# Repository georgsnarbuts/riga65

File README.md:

# riga65

<br />This work is licensed under a <a rel="license" href="http://creativecommons.org/licenses/by-nc/4.0/">Creative Commons Attribution-NonCommercial 4.0 International License</a>.  

a 65 % keyboard

A custom 65% mechanical keyboard with 100% through hole component assembly.  
Running atMega 32a MCU.  
Featuring a 128x32 oled display and an optional rotary encoder. Running QMK.    
  
Sample board built with gateron yellow switches (filmed and lubed with krytox 205 grade 0) and durock stabilizers.

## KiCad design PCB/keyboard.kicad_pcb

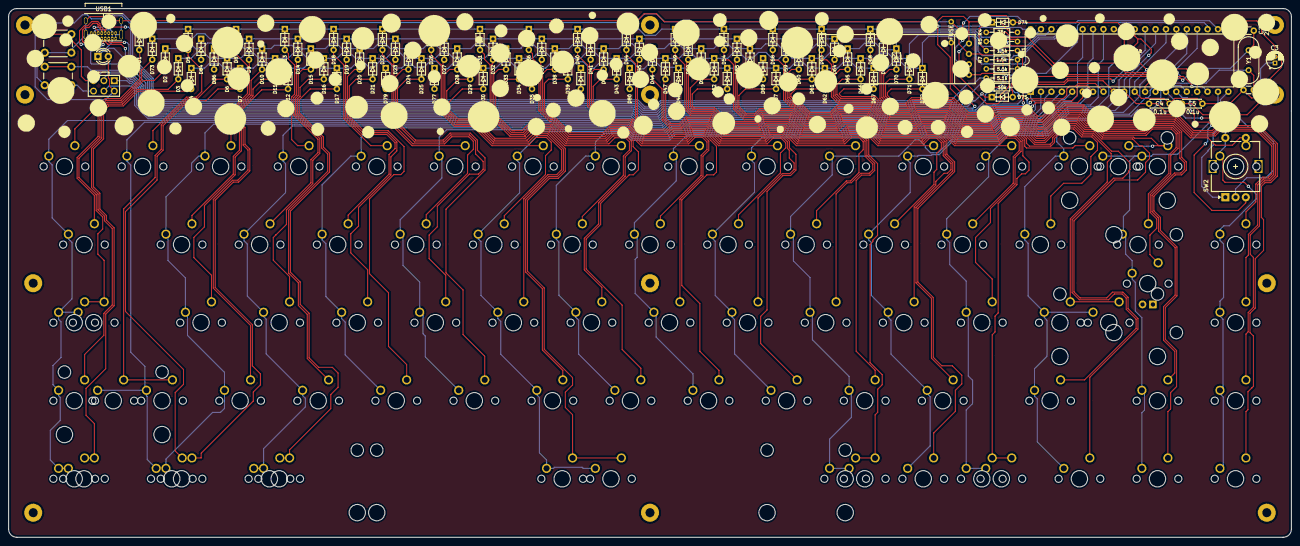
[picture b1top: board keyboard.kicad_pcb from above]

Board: 2 copper layers, 313.0 x 129.0 mm, 185 parts (0 on the bottom side), 114 nets.

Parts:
C1, C2: 22p; C_Disc_D3.0mm_W1.6mm_P2.50mm
C3: 4.7u; CP_Radial_D4.0mm_P1.50mm
C4, C5: 0.1u; C_Disc_D4.3mm_W1.9mm_P5.00mm
D1, D2, D3, D4, D5, D6, D7, D8, D9, D10, D11, D12, D13, D14, D15, D16, D17, D18, D19, D20, D21, D22, D23, D24, D25, D26, D27, D28, D29, D30, D31, D32, D33, D34, D35, D36, D37, D38, D39, D40, D41, D42, D43, D44, D45, D46, D47, D48, D49, D50, D51, D52, D53, D54, D55, D56, D57, D58, D59, D60, D61, D62, D63, D64, D65, D66, D67, D68, D69, D70, D71, D72, D73, D77, D79, D80, D81, D84, D86, D89: 1N4148; D_DO-35_SOD27_P5.08mm_Horizontal
D74, D75: D_Zener_Small; D_DO-35_SOD27_P5.08mm_Horizontal
D76: LED; LED_D3.0mm
F1: 500mA; polyfuse_5.1mm
J1: AVR-ISP-6; AVR_ICSP_3x2
K_1.5U_LALT1, K_1.5U_LCTRL1, K_1.5U_RALT1, K_1.5U_RCTRL1: KEYSW; MXOnly-1.5U-NoLED
K_1.25U_LALT1, K_1.25U_LCNTRL1, K_1.25U_LWIN1: KEYSW; MXOnly-1.25U-NoLED
K_1U_BACKSPACE1, K_1U_LCTRL1, K_1U_RALT1, K_1U_RCTRL1, K_1U_RWIN1, K_.1: KEYSW; MXOnly-1U-NoLED
K_2U_BACKSPACE1: KEYSW; MXOnly-2U-NoLED
K_6.25U_SPACE1: KEYSW; MXOnly-6.25U-NoLED
K_7U_SPACE1: KEYSW; MXOnly-7U-NoLED
K_'1: KEYSW; MXOnly-1U-NoLED
K_,1: KEYSW; MXOnly-1U-NoLED
K_-1: KEYSW; MXOnly-1U-NoLED
K_/1: KEYSW; MXOnly-1U-NoLED
K_;1: KEYSW; MXOnly-1U-NoLED
K_=1: KEYSW; MXOnly-1U-NoLED
K_A1: KEYSW; MXOnly-1U-NoLED
K_ANSI\1: KEYSW; MXOnly-1.5U-NoLED
K_ANSI_ENTER1: KEYSW; MXOnly-2.25U-NoLED
K_ANSI_LSHIFT1: KEYSW; MXOnly-2.25U-NoLED
K_ARROWDOWN1: KEYSW; MXOnly-1U-NoLED
K_ARROWUP1: KEYSW; MXOnly-1U-NoLED
K_B1: KEYSW; MXOnly-1U-NoLED
K_C1: KEYSW; MXOnly-1U-NoLED
K_CAPS1: KEYSW; MXOnly-1.75U-NoLED
K_D1: KEYSW; MXOnly-1U-NoLED
K_E1: KEYSW; MXOnly-1U-NoLED
K_EIGHT1: KEYSW; MXOnly-1U-NoLED
K_END1: KEYSW; MXOnly-1U-NoLED
K_ESC1: KEYSW; MXOnly-1U-NoLED
K_F1: KEYSW; MXOnly-1U-NoLED
K_FIVE1: KEYSW; MXOnly-1U-NoLED
K_FOUR1: KEYSW; MXOnly-1U-NoLED
K_G1: KEYSW; MXOnly-1U-NoLED
K_H1: KEYSW; MXOnly-1U-NoLED
K_I1: KEYSW; MXOnly-1U-NoLED
K_ISO_LSHIFT1: KEYSW; MXOnly-1.25U-NoLED
K_ISO_\1: KEYSW; MXOnly-1U-NoLED
K_J1: KEYSW; MXOnly-1U-NoLED
K_K1: KEYSW; MXOnly-1U-NoLED
K_L1: KEYSW; MXOnly-1U-NoLED
K_L_ARROW1: KEYSW; MXOnly-1U-NoLED
K_M1: KEYSW; MXOnly-1U-NoLED
K_N1: KEYSW; MXOnly-1U-NoLED
K_NINE1: KEYSW; MXOnly-1U-NoLED
K_O1: KEYSW; MXOnly-1U-NoLED
K_ONE1: KEYSW; MXOnly-1U-NoLED
K_P1: KEYSW; MXOnly-1U-NoLED
K_PAGEDOWN1: KEYSW; MXOnly-1U-NoLED
K_PAGE_UP1: KEYSW; MXOnly-1U-NoLED
K_Q1: KEYSW; MXOnly-1U-NoLED
K_R1: KEYSW; MXOnly-1U-NoLED
K_RANDOM_1U1: KEYSW; MXOnly-1U-NoLED
K_RSHIFT1: KEYSW; MXOnly-1.75U-NoLED
K_R_ARROW1, K_R_ARROW2: KEYSW; MXOnly-1U-NoLED
K_S1: KEYSW; MXOnly-1U-NoLED
K_SEVEN1: KEYSW; MXOnly-1U-NoLED
K_SIX1: KEYSW; MXOnly-1U-NoLED
K_STEPPED_CAPS1: KEYSW; MXOnly-1.25U-NoLED
K_T1: KEYSW; MXOnly-1U-NoLED
K_TAB1: KEYSW; MXOnly-1.5U-NoLED
K_THREE1: KEYSW; MXOnly-1U-NoLED
K_TWO1: KEYSW; MXOnly-1U-NoLED
K_U1: KEYSW; MXOnly-1U-NoLED
K_V1: KEYSW; MXOnly-1U-NoLED
K_W1: KEYSW; MXOnly-1U-NoLED
K_X1: KEYSW; MXOnly-1U-NoLED
K_Y1: KEYSW; MXOnly-1U-NoLED
K_Z1: KEYSW; MXOnly-1U-NoLED
K_ZERO1: KEYSW; MXOnly-1U-NoLED
K_[1: KEYSW; MXOnly-1U-NoLED
K_]1: KEYSW; MXOnly-1U-NoLED
K_isoenter1: KEYSW; MXOnly-ISO-ReversedStabilizers
OL1: OLED-kbd; ssd1306 128x32 oled
R1, R7: 1.5k; R_Axial_DIN0204_L3.6mm_D1.6mm_P7.62mm_Horizontal
R2, R3: 5.1k; R_Axial_DIN0204_L3.6mm_D1.6mm_P7.62mm_Horizontal
R4, R5: 75r; R_Axial_DIN0204_L3.6mm_D1.6mm_P7.62mm_Horizontal
R6: 10k; R_Axial_DIN0204_L3.6mm_D1.6mm_P7.62mm_Horizontal
SW1: boot switch; SW_PUSH_6mm
SW2: Rotary_Encoder_Switch-Device-LCK75-rescue; RotaryEncoder_Alps_EC11E-Switch_Vertical_H20mm
SW3: reset switch; SW_PUSH_6mm
U1: atmega; DIP-40_W15.24mm
USB1: Type-C_USB_C_GCT_USB4085-mysterium-pcb-cache; USB_C_GCT_USB4085
Y1: Crystal; Crystal_HC49-4H_Vertical
`1: KEYSW; MXOnly-1U-NoLED

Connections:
D+: R5.1, U1.16
D-: R4.1, U1.17
EC11-A: SW2.A, U1.14
EC11-B: SW2.B, U1.15
EC11-GND: C1.2, C2.2, C3.2, C4.2, C5.2, D74.2, D75.2, J1.6, OL1.4, R2.1, R3.1, R7.2, SW1.1, SW2.C, SW3.1, U1.11, U1.31, USB1.A1, USB1.B1, USB1.B12, USB1.S1
MISO: J1.1, U1.7
MOSI: J1.4, U1.6
unnamed: C1.1, U1.13, Y1.1
unnamed: C2.1, U1.12, Y1.2
unnamed: D1.2, K_ESC1.2
unnamed: D2.2, K_CAPS1.2, K_STEPPED_CAPS1.2
unnamed: D3.2, K_ISO_LSHIFT1.2
unnamed: D4.2, K_1.5U_LCTRL1.2, K_1.25U_LCNTRL1.2
unnamed: D5.2, K_ONE1.2
unnamed: D6.2, K_ANSI_LSHIFT1.2, K_ISO_\1.2
unnamed: D7.2, K_1.25U_LWIN1.2
unnamed: D8.2, K_TWO1.2
unnamed: D9.2, K_Q1.2
unnamed: D10.2, K_A1.2
unnamed: D11.2, K_Z1.2
unnamed: D12.2, K_1U_LCTRL1.2
unnamed: D13.2, K_THREE1.2
unnamed: D14.2, K_W1.2
unnamed: D15.2, K_S1.2
unnamed: D16.2, K_X1.2
unnamed: D17.2, K_1.5U_LALT1.2, K_1.25U_LALT1.2
unnamed: D18.2, K_FOUR1.2
unnamed: D19.2, K_E1.2
unnamed: D20.2, K_D1.2
unnamed: D21.2, K_C1.2
unnamed: D22.2, K_FIVE1.2
unnamed: D23.2, K_R1.2
unnamed: D24.2, K_F1.2
unnamed: D25.2, K_V1.2
unnamed: D26.2, K_SIX1.2
unnamed: D27.2, K_T1.2
unnamed: D28.2, K_G1.2
unnamed: D29.2, K_B1.2
unnamed: D30.2, K_6.25U_SPACE1.2, K_7U_SPACE1.2
unnamed: D31.2, K_SEVEN1.2
unnamed: D32.2, K_Y1.2
unnamed: D33.2, K_H1.2
unnamed: D34.2, K_N1.2
unnamed: D36.2, K_EIGHT1.2
unnamed: D37.2, K_U1.2
unnamed: D38.2, K_J1.2
unnamed: D39.2, K_M1.2
unnamed: D40.2, K_NINE1.2
unnamed: D41.2, K_I1.2
unnamed: D42.2, K_K1.2
unnamed: D43.2, K_,1.2
unnamed: D44.2, K_ZERO1.2
unnamed: D45.2, K_O1.2
unnamed: D46.2, K_L1.2
unnamed: D47.2, K_.1.2
unnamed: D48.2, K_1.5U_RALT1.2, K_1U_RALT1.2
unnamed: D49.2, K_-1.2
unnamed: D50.2, K_P1.2
unnamed: D51.2, K_;1.2
unnamed: D52.2, K_/1.2
unnamed: D53.2, K_1U_RWIN1.2
unnamed: D54.2, K_=1.2
unnamed: D55.2, K_[1.2
unnamed: D56.2, K_'1.2
unnamed: D57.2, K_1.5U_RCTRL1.2, K_1U_RCTRL1.2
unnamed: D58.2, K_RANDOM_1U1.2
unnamed: D59.2, K_]1.2
unnamed: D60.2, K_ANSI_ENTER1.2, `1.2
unnamed: D61.2, K_RSHIFT1.2
unnamed: D62.2, K_L_ARROW1.2
unnamed: D63.2, K_1U_BACKSPACE1.2, K_2U_BACKSPACE1.2
unnamed: D64.2, K_ANSI\1.2
unnamed: D65.2, K_isoenter1.2
unnamed: D66.2, K_ARROWUP1.2
unnamed: D67.2, K_ARROWDOWN1.2
unnamed: D68.2, K_R_ARROW2.2, SW2.S1
unnamed: D69.2, K_PAGE_UP1.2
unnamed: D70.2, K_PAGEDOWN1.2
unnamed: D71.2, K_END1.2
unnamed: D72.2, K_R_ARROW1.2
unnamed: D73.2, K_TAB1.2
unnamed: D74.1, R1.2, R4.2, USB1.A7, USB1.B7
unnamed: D75.1, R5.2, USB1.A6, USB1.B6
unnamed: D76.1, R7.1
unnamed: R2.2, USB1.B5
unnamed: R3.2, USB1.A5
SCK: J1.3, U1.8
VCC: F1.2, USB1.A4, USB1.A9, USB1.B4, USB1.B9
boot: SW1.2, U1.18
col0: K_1.5U_LCTRL1.1, K_1.25U_LCNTRL1.1, K_CAPS1.1, K_ESC1.1, K_ISO_LSHIFT1.1, K_STEPPED_CAPS1.1, K_TAB1.1, U1.1
col1: K_1.25U_LWIN1.1, K_ANSI_LSHIFT1.1, K_ISO_\1.1, K_ONE1.1, U1.2
col2: K_1U_LCTRL1.1, K_A1.1, K_Q1.1, K_TWO1.1, K_Z1.1, U1.3
col3: K_1.5U_LALT1.1, K_1.25U_LALT1.1, K_S1.1, K_THREE1.1, K_W1.1, K_X1.1, U1.4
col4: K_C1.1, K_D1.1, K_E1.1, K_FOUR1.1, U1.5
col5: K_F1.1, K_FIVE1.1, K_R1.1, K_V1.1, U1.35
col6: K_6.25U_SPACE1.1, K_7U_SPACE1.1, K_B1.1, K_G1.1, K_SIX1.1, K_T1.1, U1.34
col7: K_H1.1, K_N1.1, K_SEVEN1.1, K_Y1.1, U1.33
col8: K_EIGHT1.1, K_J1.1, K_M1.1, K_U1.1, U1.29
col9: K_,1.1, K_I1.1, K_K1.1, K_NINE1.1, U1.28
col10: K_1.5U_RALT1.1, K_1U_RALT1.1, K_.1.1, K_L1.1, K_O1.1, K_ZERO1.1, U1.27
col11: K_1U_RWIN1.1, K_-1.1, K_/1.1, K_;1.1, K_P1.1, U1.26
col12: K_1.5U_RCTRL1.1, K_1U_RCTRL1.1, K_'1.1, K_=1.1, K_[1.1, U1.25
col13: K_ANSI_ENTER1.1, K_L_ARROW1.1, K_RANDOM_1U1.1, K_RSHIFT1.1, K_]1.1, U1.24, `1.1
col14: K_1U_BACKSPACE1.1, K_2U_BACKSPACE1.1, K_ANSI\1.1, K_ARROWDOWN1.1, K_ARROWUP1.1, K_isoenter1.1, U1.19
col15: K_END1.1, K_PAGEDOWN1.1, K_PAGE_UP1.1, K_R_ARROW1.1, K_R_ARROW2.1, SW2.S2, U1.20
oledSCL: OL1.2, U1.22
oledSDA: OL1.1, U1.23
oledVCC1: C3.1, C4.1, C5.1, D76.2, F1.1, J1.2, OL1.3, R1.1, R6.1, U1.10, U1.30
reset: J1.5, R6.2, SW3.2, U1.9
row0: D1.1, D5.1, D8.1, D13.1, D18.1, D22.1, D26.1, D31.1, D36.1, D40.1, D44.1, D49.1, D54.1, D58.1, D63.1, D68.1, U1.40
row1: D9.1, D14.1, D19.1, D23.1, D27.1, D32.1, D37.1, D41.1, D45.1, D50.1, D55.1, D59.1, D64.1, D69.1, D73.1, U1.39
row2: D2.1, D10.1, D15.1, D20.1, D24.1, D28.1, D33.1, D38.1, D42.1, D46.1, D51.1, D56.1, D60.1, D65.1, D70.1, U1.38
row3: D3.1, D6.1, D11.1, D16.1, D21.1, D25.1, D29.1, D34.1, D39.1, D43.1, D47.1, D52.1, D61.1, D66.1, D71.1, U1.37
row4: D4.1, D7.1, D12.1, D17.1, D30.1, D48.1, D53.1, D57.1, D62.1, D67.1, D72.1, U1.36

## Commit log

2021-12-30 kicad files
2022-02-10 better organisation
    reorganised for better readability
2022-02-10 QMK firmware
    qmk firmware. **Only the ISO variant is checked working!**
2022-02-10 qmk firmware
